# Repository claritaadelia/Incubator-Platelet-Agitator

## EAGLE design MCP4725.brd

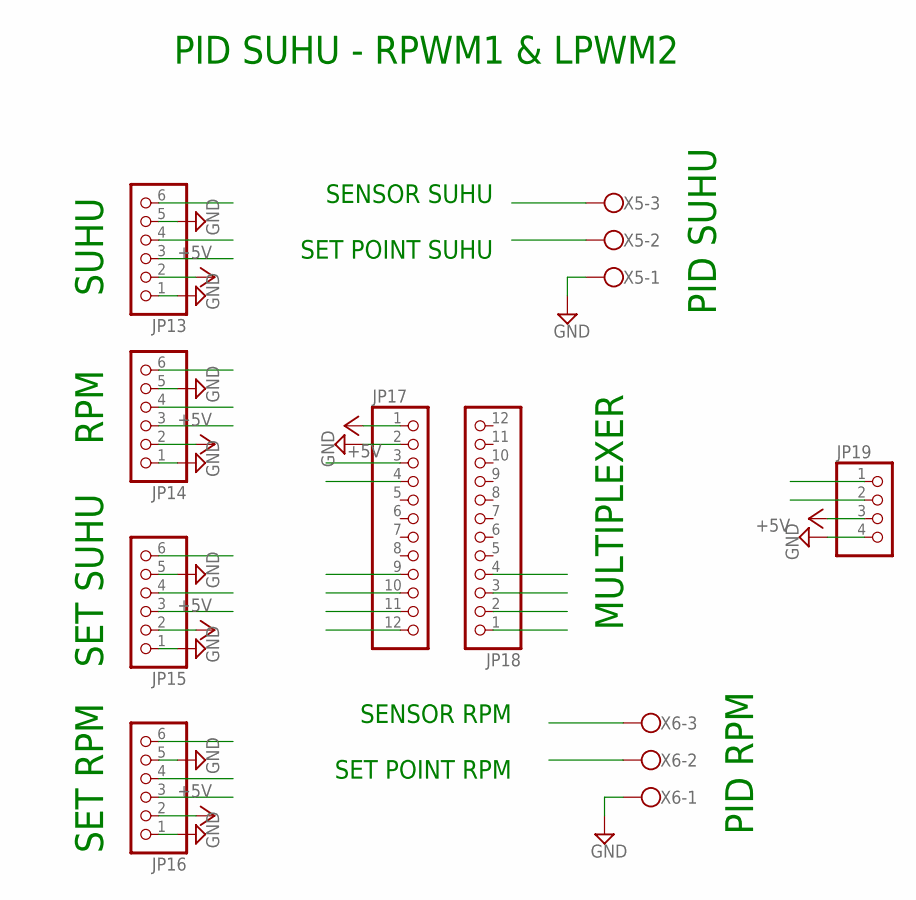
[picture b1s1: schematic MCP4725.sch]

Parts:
JP13, JP14, JP15, JP16: PINHD-1X6; 1X06
JP17, JP18: PINHD-1X12; 1X12
JP19: PINHD-1X4; 1X04
X5, X6: W237-103

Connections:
+5V: JP13.2, JP14.2, JP15.2, JP16.2, JP17.1, JP19.3
GND: JP13.1, JP13.5, JP14.1, JP14.5, JP15.1, JP15.5, JP16.1, JP16.5, JP17.2, JP19.4, X5.1, X6.1
unnamed: JP13.3, JP17.9
unnamed: JP13.4, JP17.10
unnamed: JP14.3, JP17.11
unnamed: JP14.4, JP17.12
unnamed: JP15.3, JP18.1
unnamed: JP15.4, JP18.2
unnamed: JP16.4, JP18.4
unnamed: JP16.3, JP18.3
unnamed: JP17.3, JP19.2
unnamed: JP17.4, JP19.1
unnamed: JP15.6, X5.2
unnamed: JP13.6, X5.3
unnamed: JP14.6, X6.3
unnamed: JP16.6, X6.2

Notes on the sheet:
SUHU
PID RPM
SET SUHU
RPM
SET RPM
PID SUHU
MULTIPLEXER
SENSOR SUHU
SET POINT SUHU
SENSOR RPM
SET POINT RPM
PID SUHU - RPWM1 & LPWM2

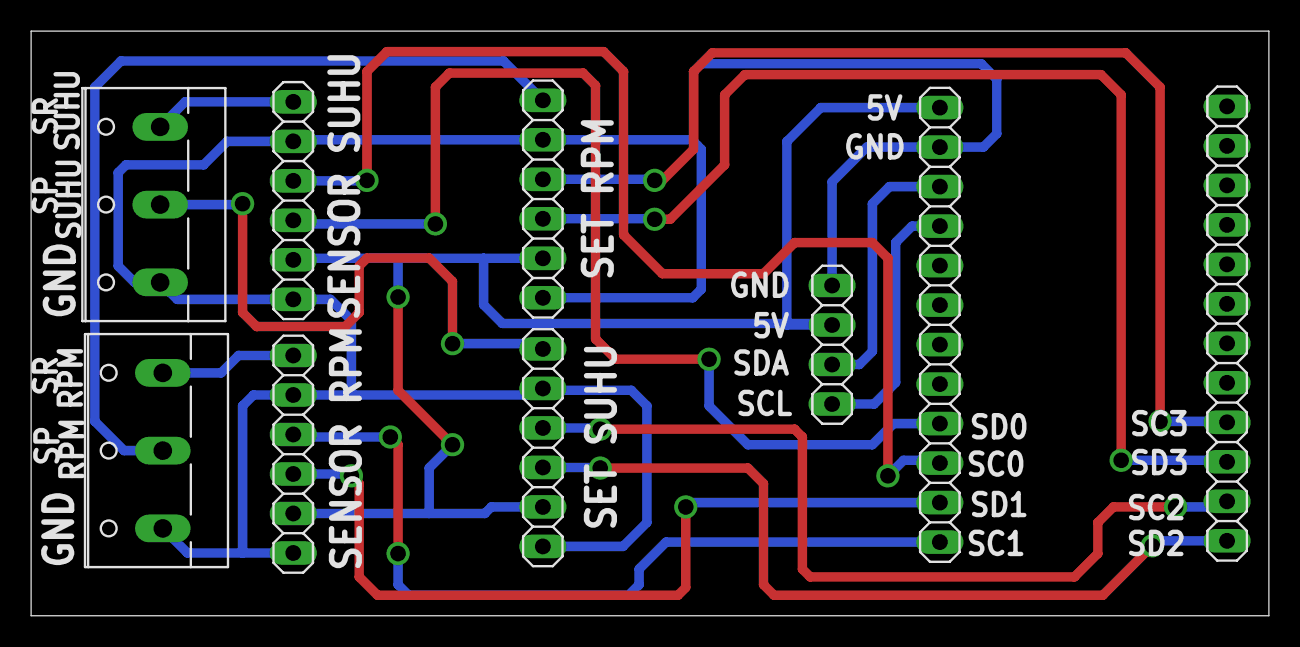
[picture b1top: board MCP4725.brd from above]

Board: 2 copper layers, 79.6 x 37.6 mm, 9 parts (0 on the bottom side), 16 nets.

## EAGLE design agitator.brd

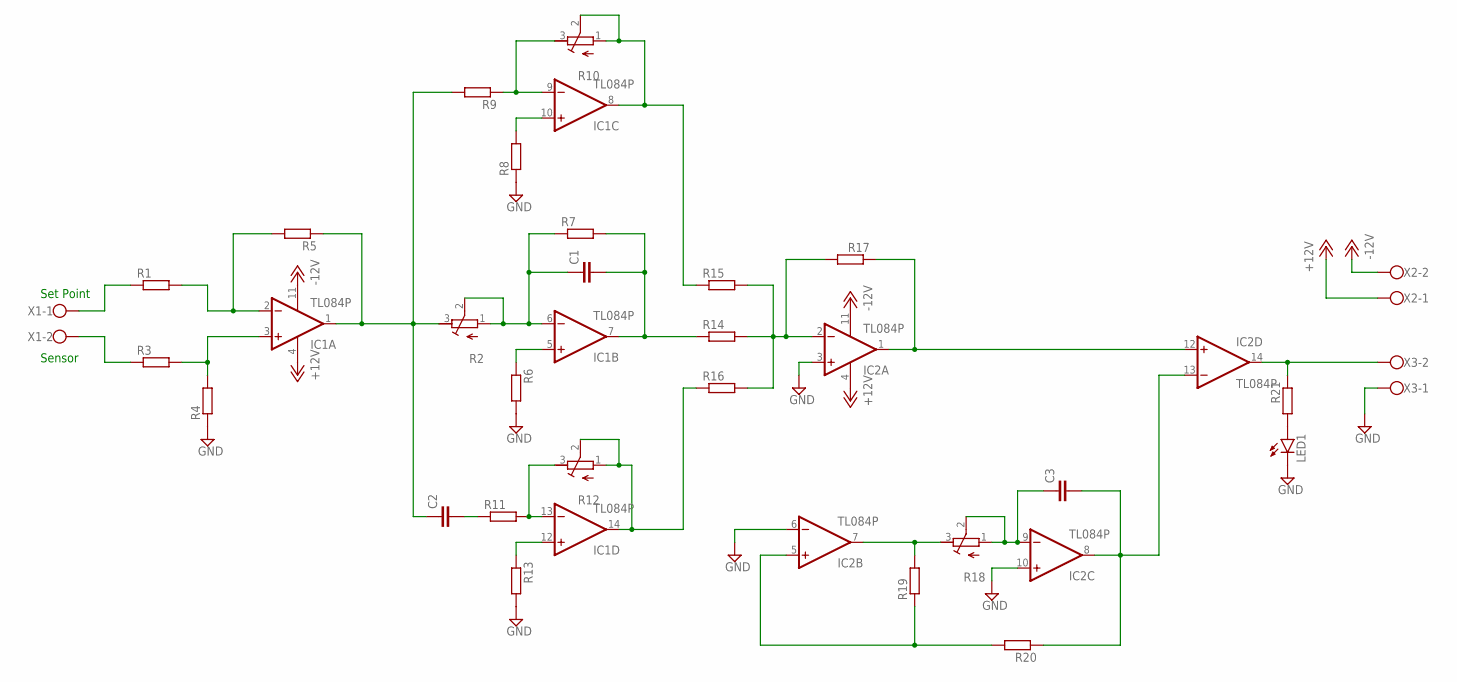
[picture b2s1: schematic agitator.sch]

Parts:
C1, C2, C3: C2.5/2; C2.5-2
IC1, IC2: TL084P; DIL14
LED1: LED3MM
R1, R3, R4, R5, R6, R7, R8, R9, R11, R13, R14, R15, R16, R17, R19, R20, R21: R-EU_0207/10; 0207/10
R2, R10, R12, R18: R-TRIMM64W; RTRIM64W
X1, X2, X3: W237-102

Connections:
+12V: IC1.4 (V+), IC2.4 (V+), X2.1
-12V: IC1.11 (V-), IC2.11 (V-), X2.2
GND: IC2.3 (+IN), IC2.6 (-IN), IC2.10 (+IN), LED1.K (C), R4.1, R6.2, R8.1, R13.2, X3.1
unnamed: IC1.3 (+IN), R3.2, R4.2
unnamed: IC1.2 (-IN), R1.2, R5.2
unnamed: C2.1, IC1.1 (OUT), R2.3 (E), R5.1, R9.2
unnamed: R1.1, X1.1
unnamed: R3.1, X1.2
unnamed: C1.1, IC1.6 (-IN), R2.1 (A), R2.2 (S), R7.1
unnamed: C1.2, IC1.7 (OUT), R7.2, R14.1
unnamed: IC1.5 (+IN), R6.1
unnamed: IC1.10 (+IN), R8.2
unnamed: IC1.9 (-IN), R9.1, R10.3 (E)
unnamed: C2.2, R11.1
unnamed: IC1.8 (OUT), R10.1 (A), R10.2 (S), R15.1
unnamed: IC1.13 (-IN), R11.2, R12.3 (E)
unnamed: IC1.14 (OUT), R12.1 (A), R12.2 (S), R16.1
unnamed: IC1.12 (+IN), R13.1
unnamed: IC2.2 (-IN), R14.2, R15.2, R16.2, R17.2
unnamed: IC2.1 (OUT), IC2.12 (+IN), R17.1
unnamed: IC2.7 (OUT), R18.3 (E), R19.2
unnamed: C3.1, IC2.9 (-IN), R18.1 (A), R18.2 (S)
unnamed: LED1.A, R21.2
unnamed: IC2.5 (+IN), R19.1, R20.2
unnamed: C3.2, IC2.8 (OUT), IC2.13 (-IN), R20.1
unnamed: IC2.14 (OUT), R21.1, X3.2

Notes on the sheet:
Set Point
Sensor

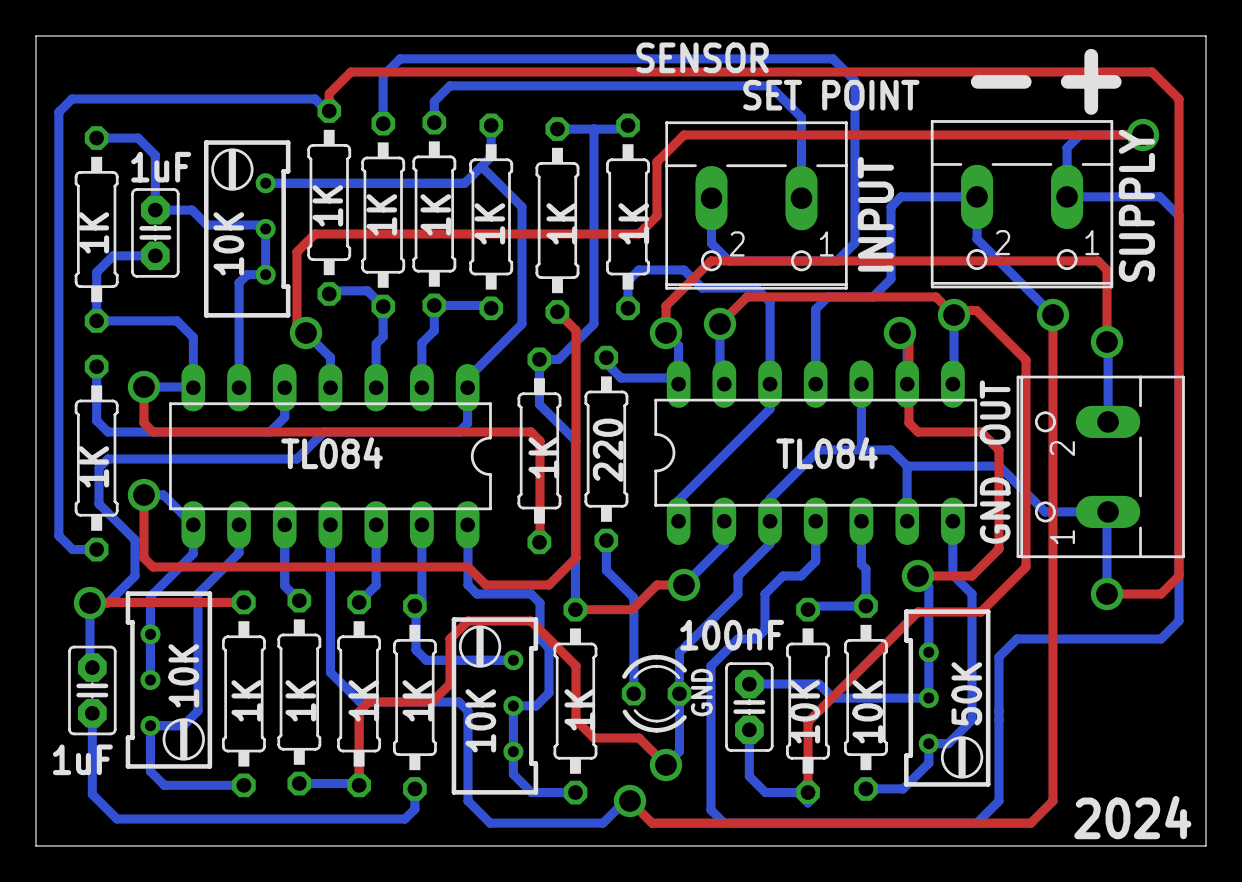
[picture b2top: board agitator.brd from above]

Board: 2 copper layers, 65.0 x 45.0 mm, 30 parts (0 on the bottom side), 26 nets.

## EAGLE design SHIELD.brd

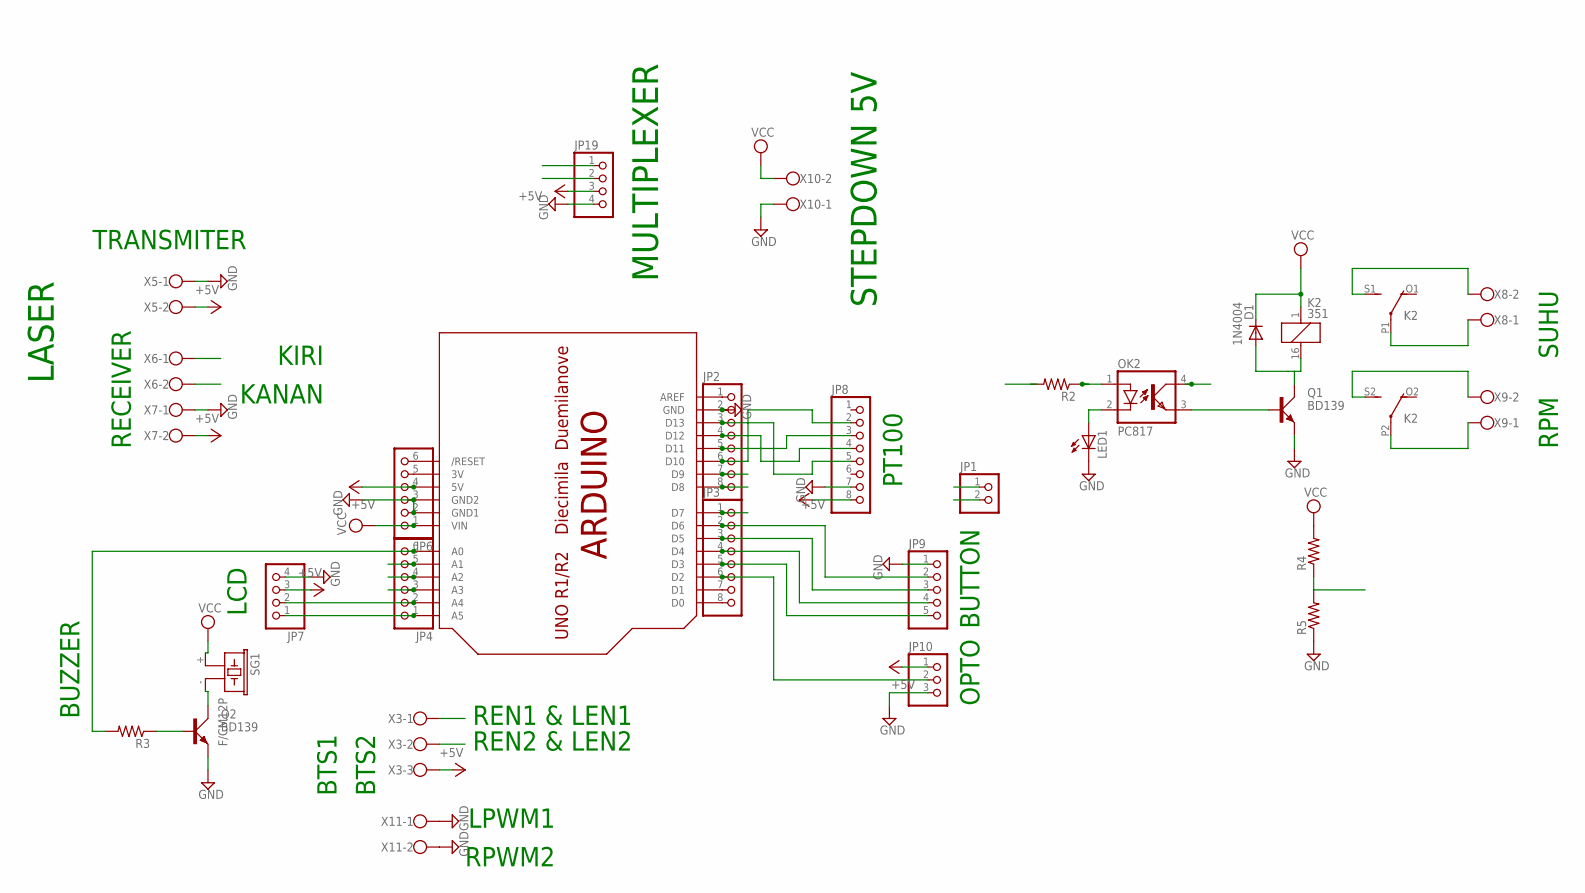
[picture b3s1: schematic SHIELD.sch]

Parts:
D1: 1N4004; DO41-10
JP1: PINHD-1X2; 1X02
JP2, JP3, JP8: PINHD-1X8; 1X08
JP4, JP6: PINHD-1X6; 1X06
JP7, JP19: PINHD-1X4; 1X04
JP9: PINHD-1X5; 1X05
JP10: PINHD-1X3; 1X03
K2: 351
LED1: LED5MM
OK2: PC817; DIL04
Q1, Q2: BD139; TO126AV
R2, R3, R4, R5: R-US_0207/10; 0207/10
SG1: F/CM12P
U$1: ARDUINO-NOHOLE
X3: W237-103
X5, X6, X7, X8, X9, X10, X11: W237-102

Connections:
+5V: JP6.4, JP7.3, JP8.8, JP10.1, JP19.3, U$1.5V, X3.3, X5.2, X7.2
GND: JP2.2, JP6.2, JP6.3, JP7.4, JP8.7, JP9.1, JP10.3, JP19.4, LED1.K (C), Q1.E, Q2.E, R5.1, U$1.GND, U$1.GND1, U$1.GND2, X5.1, X7.1, X10.1, X11.1, X11.2
unnamed: JP1.1, JP1.2, JP2.7, U$1.D9
unnamed: Q2.B, R3.1
unnamed: Q2.C, SG1.- (2)
unnamed: JP2.1, U$1.AREF
unnamed: JP3.7, U$1.D1
unnamed: JP3.8, U$1.D0
unnamed: JP4.2, JP7.2, JP19.2, U$1.A4
unnamed: JP4.1, JP7.1, JP19.1, U$1.A5
unnamed: JP2.6, JP8.2, U$1.D10
unnamed: JP2.5, JP8.3, U$1.D11
unnamed: JP2.4, JP8.4, U$1.D12
unnamed: JP6.5, U$1.3V
unnamed: JP6.6, U$1.RESET (/RESET)
unnamed: JP2.3, JP8.5, U$1.D13
unnamed: JP3.5, JP9.5, U$1.D3
unnamed: JP3.4, JP9.4, U$1.D4
unnamed: JP3.3, JP9.3, U$1.D5
unnamed: JP3.2, JP9.2, U$1.D6
unnamed: JP3.6, JP10.2, U$1.D2
unnamed: JP4.6, R3.2, U$1.A0
unnamed: JP4.4, U$1.A2, X3.2
unnamed: JP3.1, U$1.D7, X6.2
unnamed: JP4.5, U$1.A1, X3.1
unnamed: JP2.8, U$1.D8, X6.1
unnamed: D1.A, K2.16 (2), Q1.C
unnamed: OK2.3 (EMIT), Q1.B
unnamed: JP4.3, R2.2, U$1.A3
unnamed: LED1.A, OK2.2 (C)
unnamed: OK2.1 (A), R2.1
unnamed: K2.S1 (S), X8.2
unnamed: K2.P2, X9.1
unnamed: OK2.4 (COL), R4.1, R5.2
unnamed: K2.S2 (S), X9.2
unnamed: K2.P1, X8.1
VCC: D1.C, JP6.1, K2.1, R4.2, SG1.+ (1), U$1.VIN, X10.2

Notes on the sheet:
LCD
BTS1
BTS2
BUZZER
TRANSMITER
RECEIVER
LASER
OPTO
BUTTON
PT100
RPM
SUHU
STEPDOWN 5V
REN1 & LEN1
REN2 & LEN2
RPWM2
LPWM1
MULTIPLEXER
KANAN
KIRI

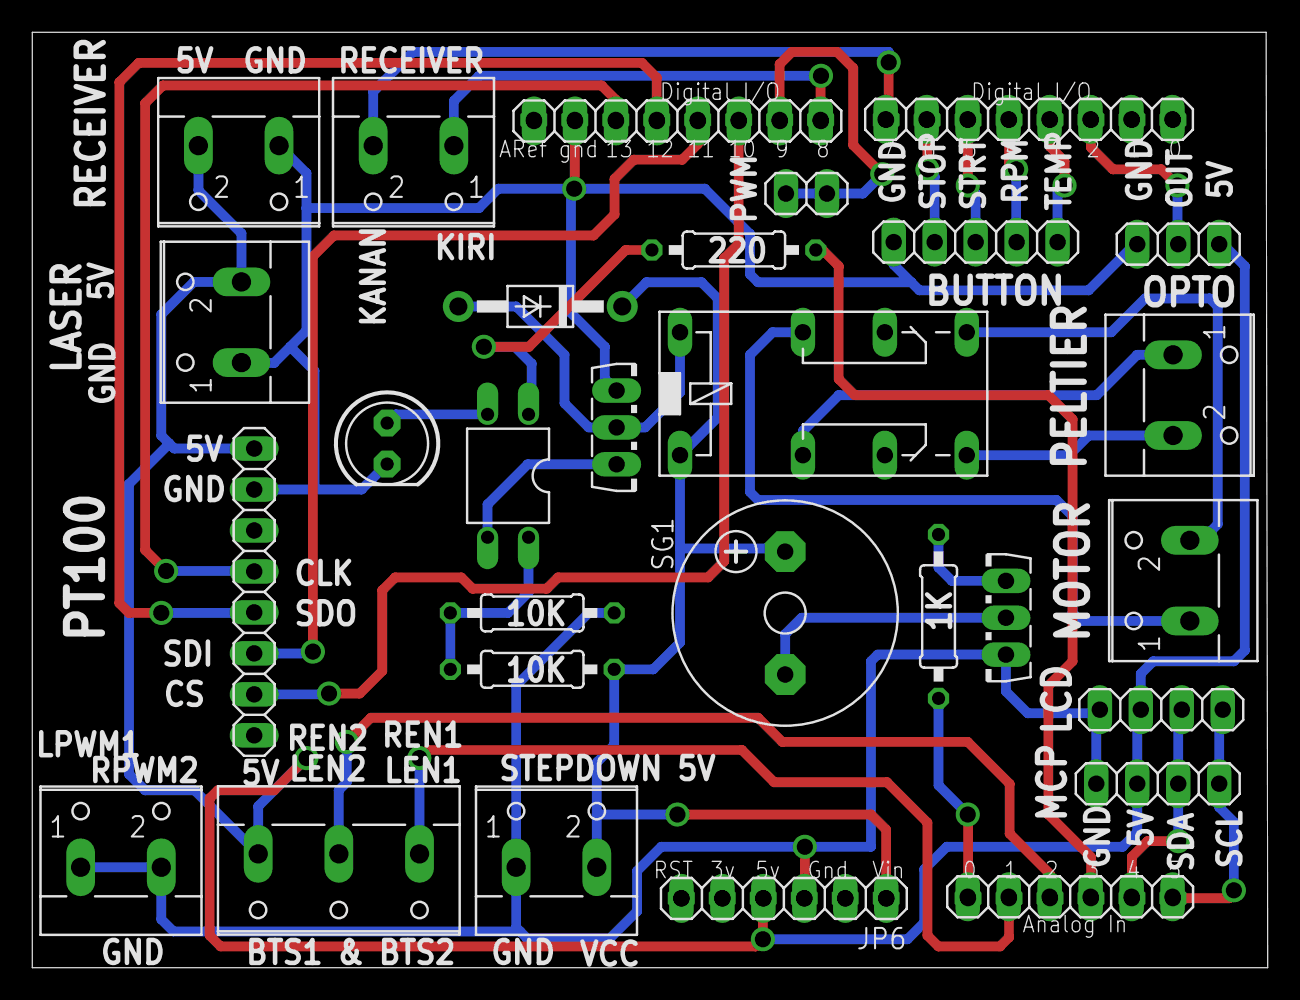
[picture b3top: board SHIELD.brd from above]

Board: 2 copper layers, 76.6 x 58.0 mm, 30 parts (0 on the bottom side), 37 nets.

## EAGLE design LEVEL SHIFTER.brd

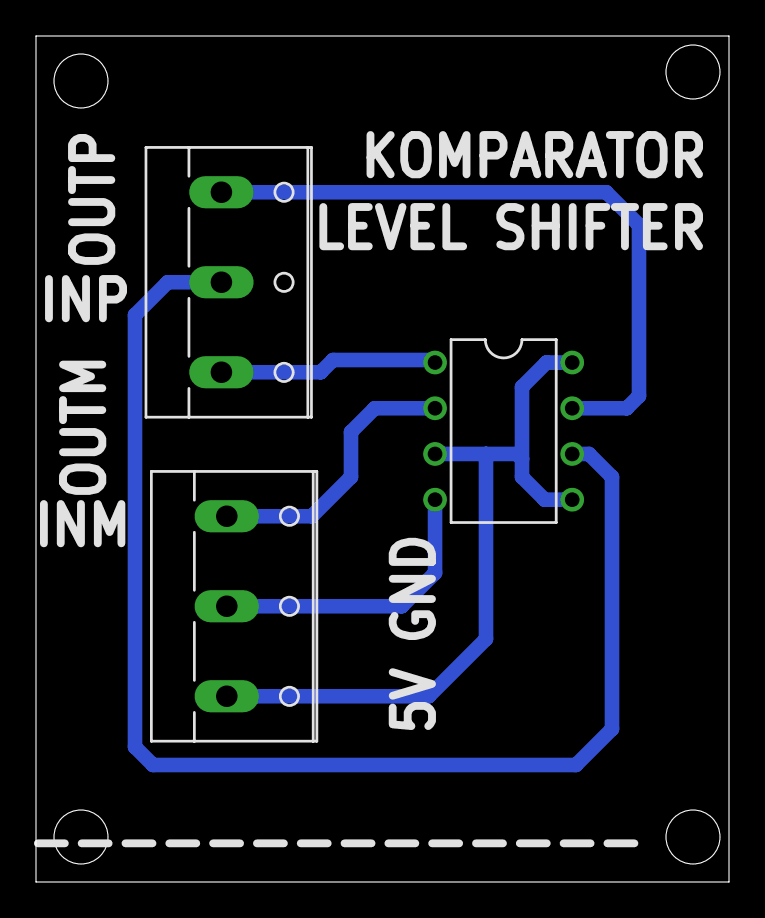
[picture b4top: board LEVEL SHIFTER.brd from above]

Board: 2 copper layers, 38.5 x 47.0 mm, 3 parts (0 on the bottom side), 6 nets.

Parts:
IC1: LM358N; DIL08
X1, X2: W237-103

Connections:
+5V: IC1.3, IC1.5, IC1.8, X1.3
GND: IC1.4, X1.2
unnamed: IC1.2, X1.1
unnamed: IC1.6, X2.2
unnamed: IC1.1, X2.3
unnamed: IC1.7, X2.1

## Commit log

2025-05-24 Rename Diagram Mekanis.jpg to Hasil Hardware.jpg
2025-05-24 Rename Screenshot 2025-05-24 184232.png to Diagram Mekanis.png
2025-05-24 Rename UPLOAD.ino to Program Keseluruhan.ino
2025-05-24 Rename Blok diagram semhas.jpg to Blok diagram.jpg
